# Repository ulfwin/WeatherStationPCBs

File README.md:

# WeatherStationPCBs
Printed Circuit Board designs for low cost weather station. See https://hackaday.io/project/5068-low-cost-weather-station

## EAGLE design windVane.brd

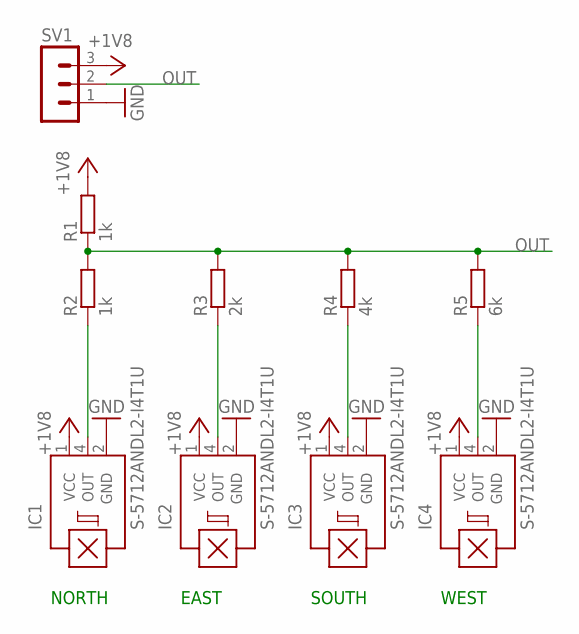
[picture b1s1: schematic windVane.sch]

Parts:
IC1, IC2, IC3, IC4: S-5712ANDL2-I4T1U; SNT-4A
R1, R2: 1k; M1206
R3: 2k; M1206
R4: 4k; M1206
R5: 6k; M1206
SV1: MA03-1

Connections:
+1V8: IC1.1 (VCC), IC2.1 (VCC), IC3.1 (VCC), IC4.1 (VCC), R1.2, SV1.3
GND: IC1.2 (GND), IC2.2 (GND), IC3.2 (GND), IC4.2 (GND), SV1.1
unnamed: IC2.4 (OUT), R3.1
unnamed: IC3.4 (OUT), R4.1
unnamed: IC4.4 (OUT), R5.1
unnamed: IC1.4 (OUT), R2.1
OUT: R1.1, R2.2, R3.2, R4.2, R5.2, SV1.2

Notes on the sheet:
NORTH
EAST
SOUTH
WEST

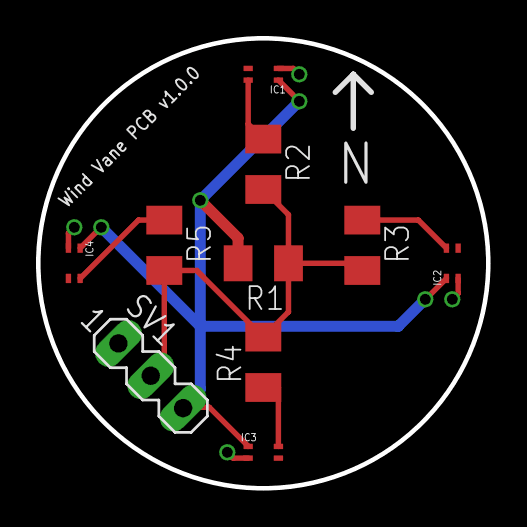
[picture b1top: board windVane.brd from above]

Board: 2 copper layers, 25.0 x 25.0 mm, 10 parts (0 on the bottom side), 7 nets.

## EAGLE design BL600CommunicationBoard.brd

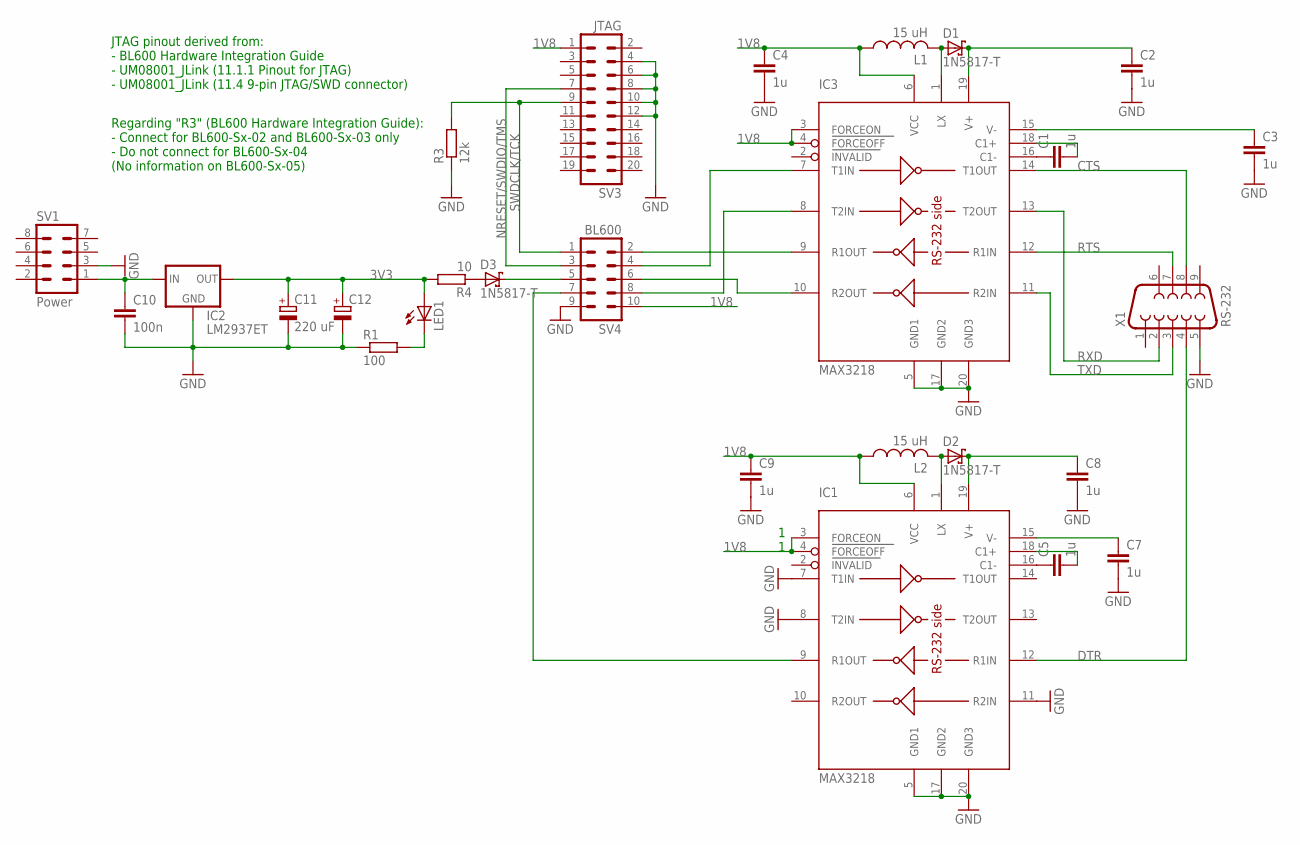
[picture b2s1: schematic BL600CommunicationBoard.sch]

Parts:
C1, C2, C3, C4, C5, C7, C8, C9: 1u; C050-025X075
C10: 100n; C050-025X075
C11: 220 uF; E2,5-6
C12: CPOL-EUE3.5-8; E3,5-8
D1, D2, D3: 1N5817-T; DO41-7.6
IC1, IC3: MAX3218; DIL20
IC2: LM2937ET; 78XXS
L1, L2: 15 uH; L1812
LED1: LED3MM
R1: 100; 0207/10
R3: 12k; 0207/10
R4: 10; 0207/10
SV1: Power; MA04-2
SV3: JTAG; MA10-2
SV4: BL600; MA05-2
X1: RS-232; F09VP

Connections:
1V8: C4.1, C9.1, IC1.3 (FORCEON), IC1.4 (FORCEOFF), IC1.6 (VCC), IC3.3 (FORCEON), IC3.4 (FORCEOFF), IC3.6 (VCC), L1.1, L2.1, SV3.1, SV4.10
3V3: C11.+, C12.+, IC2.OUT, LED1.A, R4.2
CTS: IC3.14 (T1OUT), X1.8
DTR: IC1.12 (R1IN), X1.4
GND: C2.2, C3.2, C4.2, C7.2, C8.2, C9.2, C10.2, C11.-, C12.-, IC1.5 (GND1), IC1.7 (T1IN), IC1.8 (T2IN), IC1.11 (R2IN), IC1.17 (GND2), IC1.20 (GND3), IC2.GND, IC3.5 (GND1), IC3.17 (GND2), IC3.20 (GND3), R1.1, R3.1, SV1.3, SV3.4, SV3.6, SV3.8, SV3.10, SV3.12, SV4.9, X1.5
unnamed: C10.1, IC2.IN, SV1.1
unnamed: IC3.8 (T2IN), SV4.8
unnamed: IC3.7 (T1IN), SV4.4
unnamed: IC3.9 (R1OUT), SV4.2
unnamed: IC3.10 (R2OUT), SV4.6
unnamed: D3.A, R4.1
unnamed: D3.C, SV4.5
unnamed: D1.A, IC3.1 (LX), L1.2
unnamed: C2.1, D1.C, IC3.19 (V+)
unnamed: C3.1, IC3.15 (V-)
unnamed: C1.1, IC3.16 (C1-)
unnamed: C1.2, IC3.18 (C1+)
unnamed: D2.A, IC1.1 (LX), L2.2
unnamed: LED1.K (C), R1.2
unnamed: C8.1, D2.C, IC1.19 (V+)
unnamed: C5.1, IC1.16 (C1-)
unnamed: C5.2, IC1.18 (C1+)
unnamed: C7.1, IC1.15 (V-)
unnamed: IC1.9 (R1OUT), SV4.7
NRESET/SWDIO/TMS: SV3.7, SV4.3
RTS: IC3.12 (R1IN), X1.7
RXD: IC3.13 (T2OUT), X1.2
SWDCLK/TCK: R3.2, SV3.9, SV4.1
TXD: IC3.11 (R2IN), X1.3

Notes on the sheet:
JTAG pinout derived from: - BL600 Hardware Integration Guide - UM08001_JLink (11.1.1 Pinout for JTAG) - UM08001_JLink (11.4 9-pin JTAG/SWD connector)
Regarding "R3" (BL600 Hardware Integration Guide): - Connect for BL600-Sx-02 and BL600-Sx-03 only - Do not connect for BL600-Sx-04 (No information on BL600-Sx-05)
1 1

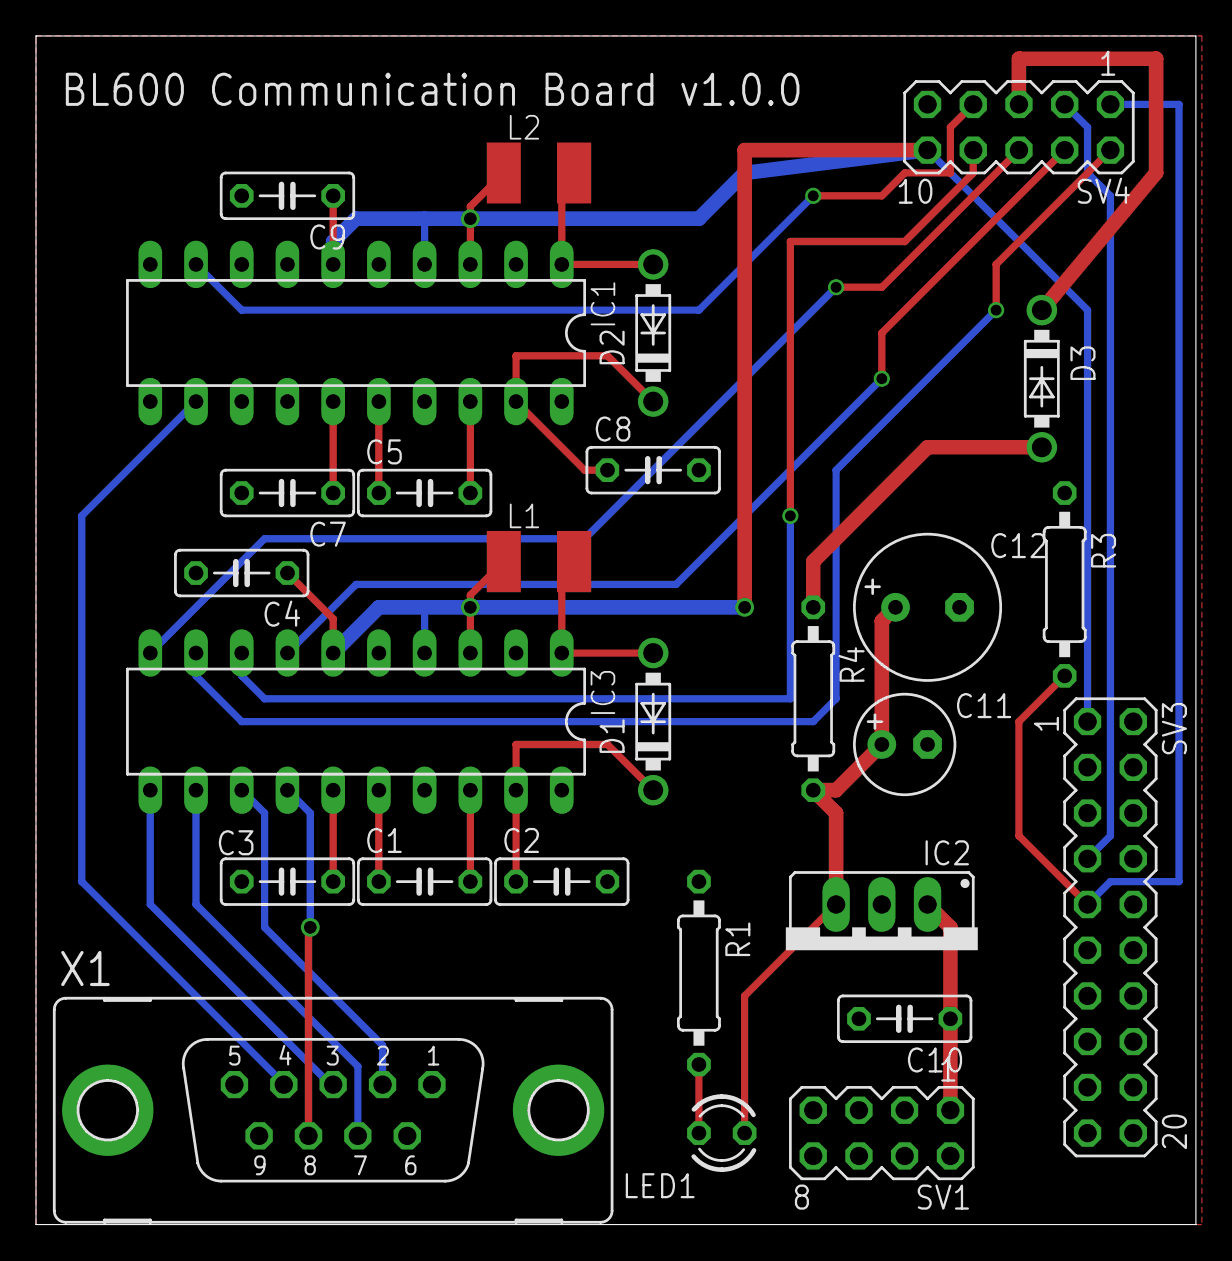
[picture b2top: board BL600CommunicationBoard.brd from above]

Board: 2 copper layers, 64.4 x 66.0 mm, 27 parts (0 on the bottom side), 29 nets.

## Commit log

2015-06-12 Made schematic
2015-07-01 Added com board layout
2015-07-01 Changed text from top layer to tPlace
2015-08-11 Added wind vane schematic and layout. DRC passes
2015-08-11 Added direction of North and PCB name and version
2015-08-23 Added LTSpice file, simulating the use of simple voltage divider and capacitor towards analog input of BL600
2015-09-16 Change placement of header pin for communication board, and changed to vector text in windVane layout
